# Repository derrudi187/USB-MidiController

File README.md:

# USB-MidiController
MidiController based on Atmel with V-USB powered by http://www.obdev.at/vusb/

Project start 06.09.2024

- 8x8 bit input matrix
	- up to 16 incremental encoders (currently working)
	- up to 32 keys	(currently working)

- up to 34 analog channels (2 channel currently working)

- up to 64 single color LEDs via SPI (not programmed)

Hardware information coming soon

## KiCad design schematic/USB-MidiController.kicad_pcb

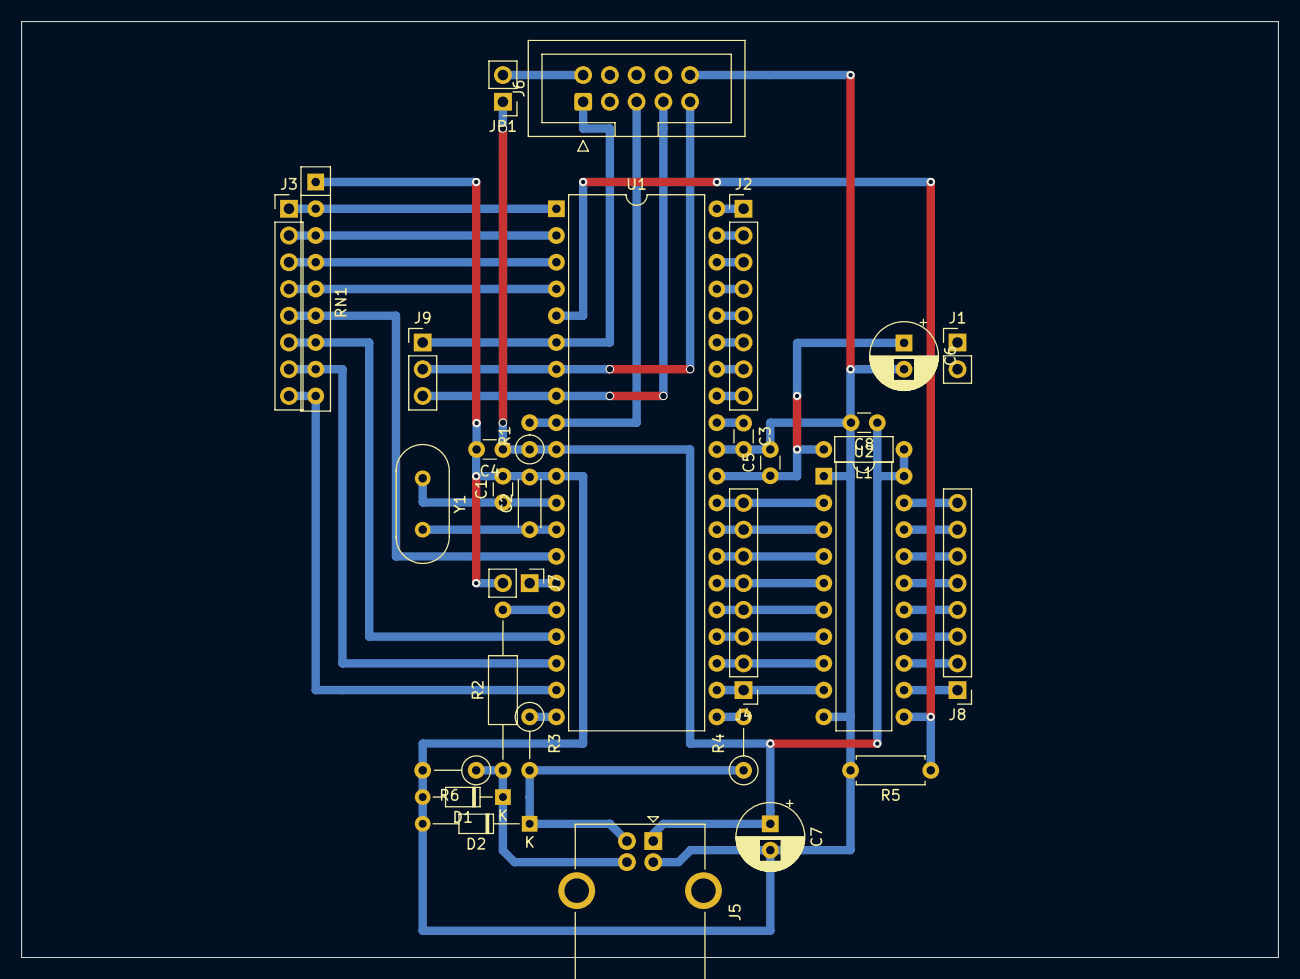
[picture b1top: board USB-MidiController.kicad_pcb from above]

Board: 2 copper layers, 119.4 x 88.9 mm, 31 parts (0 on the bottom side), 50 nets.

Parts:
C1: 22pf; C_Disc_D3.0mm_W1.6mm_P2.50mm
C2: 22pf; C_Disc_D4.3mm_W1.9mm_P5.00mm
C3, C4, C5, C8: 100nf; C_Disc_D3.0mm_W1.6mm_P2.50mm
C6, C7: 100µf; CP_Radial_D6.3mm_P2.50mm
D1: 3.3v; D_DO-34_SOD68_P7.62mm_Horizontal
D2: 3.3v; D_DO-34_SOD68_P10.16mm_Horizontal
J1: Analog-Pwr; PinHeader_1x02_P2.54mm_Vertical
J2: Analog; PinHeader_1x08_P2.54mm_Vertical
J3: Key-; PinHeader_1x08_P2.54mm_Vertical
J4: Key+; PinHeader_1x08_P2.54mm_Vertical
J5: USB_B; USB_B_OST_USB-B1HSxx_Horizontal
J6: AVR-ISP-10; IDC-Header_2x05_P2.54mm_Vertical
J7: DebugOut; PinHeader_1x02_P2.54mm_Vertical
J8: Expand; PinHeader_1x08_P2.54mm_Vertical
J9: SPI; PinHeader_1x03_P2.54mm_Vertical
JP1: ISP-Pwr; PinHeader_1x02_P2.54mm_Vertical
L1: 10mH; L_Axial_L5.3mm_D2.2mm_P7.62mm_Horizontal_Vishay_IM-1
R1: 10k; R_Axial_DIN0207_L6.3mm_D2.5mm_P2.54mm_Vertical
R2: 68R; R_Axial_DIN0207_L6.3mm_D2.5mm_P15.24mm_Horizontal
R3: 68R; R_Axial_DIN0207_L6.3mm_D2.5mm_P5.08mm_Vertical
R4: 1.5K; R_Axial_DIN0207_L6.3mm_D2.5mm_P5.08mm_Vertical
R5: 10k; R_Axial_DIN0207_L6.3mm_D2.5mm_P7.62mm_Horizontal
R6: 1M; R_Axial_DIN0207_L6.3mm_D2.5mm_P5.08mm_Vertical
RN1: 10k; R_Array_SIP9
U1: ATmega32-16PU; DIP-40_W15.24mm
U2: 74LS573; DIP-20_W7.62mm
Y1: 12Mhz; Crystal_HC49-U_Vertical

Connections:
+5V: C4.1, C7.1, C8.1, J5.1, JP1.1, L1.1, R1.1, U1.10, U2.20
/D+: R2.2, U1.16
/D-: R3.1, U1.20
/DisCon: R4.2, U1.21
/KeyIn0: J3.1, RN1.2, U1.1
/KeyIn1: J3.2, RN1.3, U1.2
/KeyIn2: J3.3, RN1.4, U1.3
/KeyIn3: J3.4, RN1.5, U1.4
/KeyIn4: J3.5, RN1.6, U1.14
/KeyIn5: J3.6, RN1.7, U1.17
/KeyIn6: J3.7, RN1.8, U1.18
/KeyIn7: J3.8, RN1.9, U1.19
/Load: R5.1, U1.5, U2.11
/MISO: J6.9, J9.2, U1.7
/MOSI: J6.1, J9.1, U1.6
/Out0: J4.1, U1.22, U2.9
/Out1: J4.2, U1.23, U2.8
/Out2: J4.3, U1.24, U2.7
/Out3: J4.4, U1.25, U2.6
/Out4: J4.5, U1.26, U2.5
/Out5: J4.6, U1.27, U2.4
/Out6: J4.7, U1.28, U2.3
/Out7: J4.8, U1.29, U2.2
/Reset: J6.5, R1.2, U1.9
/SCK: J6.7, J9.3, U1.8
/TX: J7.1, U1.15
GND: C1.2, C2.2, C3.2, C4.2, C5.2, C6.2, C7.2, C8.2, D1.2, D2.2, J1.2, J5.4, J6.4, J6.6, J6.8, J6.10, J7.2, R5.2, R6.2, RN1.1, U1.11, U1.31, U2.1, U2.10
unnamed: C1.1, U1.12, Y1.1
unnamed: C2.1, U1.13, Y1.2
unnamed: C3.1, U1.32
unnamed: C5.1, C6.1, J1.1, L1.2, U1.30
unnamed: D1.1, J5.3, R2.1, R6.1
unnamed: D2.1, J5.2, R3.2, R4.1
unnamed: J2.1, U1.40
unnamed: J2.2, U1.39
unnamed: J2.3, U1.38
unnamed: J2.4, U1.37
unnamed: J2.5, U1.36
unnamed: J2.6, U1.35
unnamed: J2.7, U1.34
unnamed: J2.8, U1.33
unnamed: J6.2, JP1.2
unnamed: J8.1, U2.12
unnamed: J8.2, U2.13
unnamed: J8.3, U2.14
unnamed: J8.4, U2.15
unnamed: J8.5, U2.16
unnamed: J8.6, U2.17
unnamed: J8.7, U2.18
unnamed: J8.8, U2.19

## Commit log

2024-09-14 project start
2024-09-14 add some files
2024-09-14 changed and add files
2024-09-15 add files and led fuction
2024-09-15 change function encoder
2024-09-15 code-lite project file changed
2024-09-15 add config_new.h
2024-09-17 edit config_new.h
2024-09-19 change config and main_new
2024-09-19 changed encoder function works
2024-09-19 key config added
2024-09-28 add technical draw
2024-09-28 technical draw changed
